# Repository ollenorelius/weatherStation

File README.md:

# weatherStation
A simple weather monitor based on an nRF52832 microcontroller

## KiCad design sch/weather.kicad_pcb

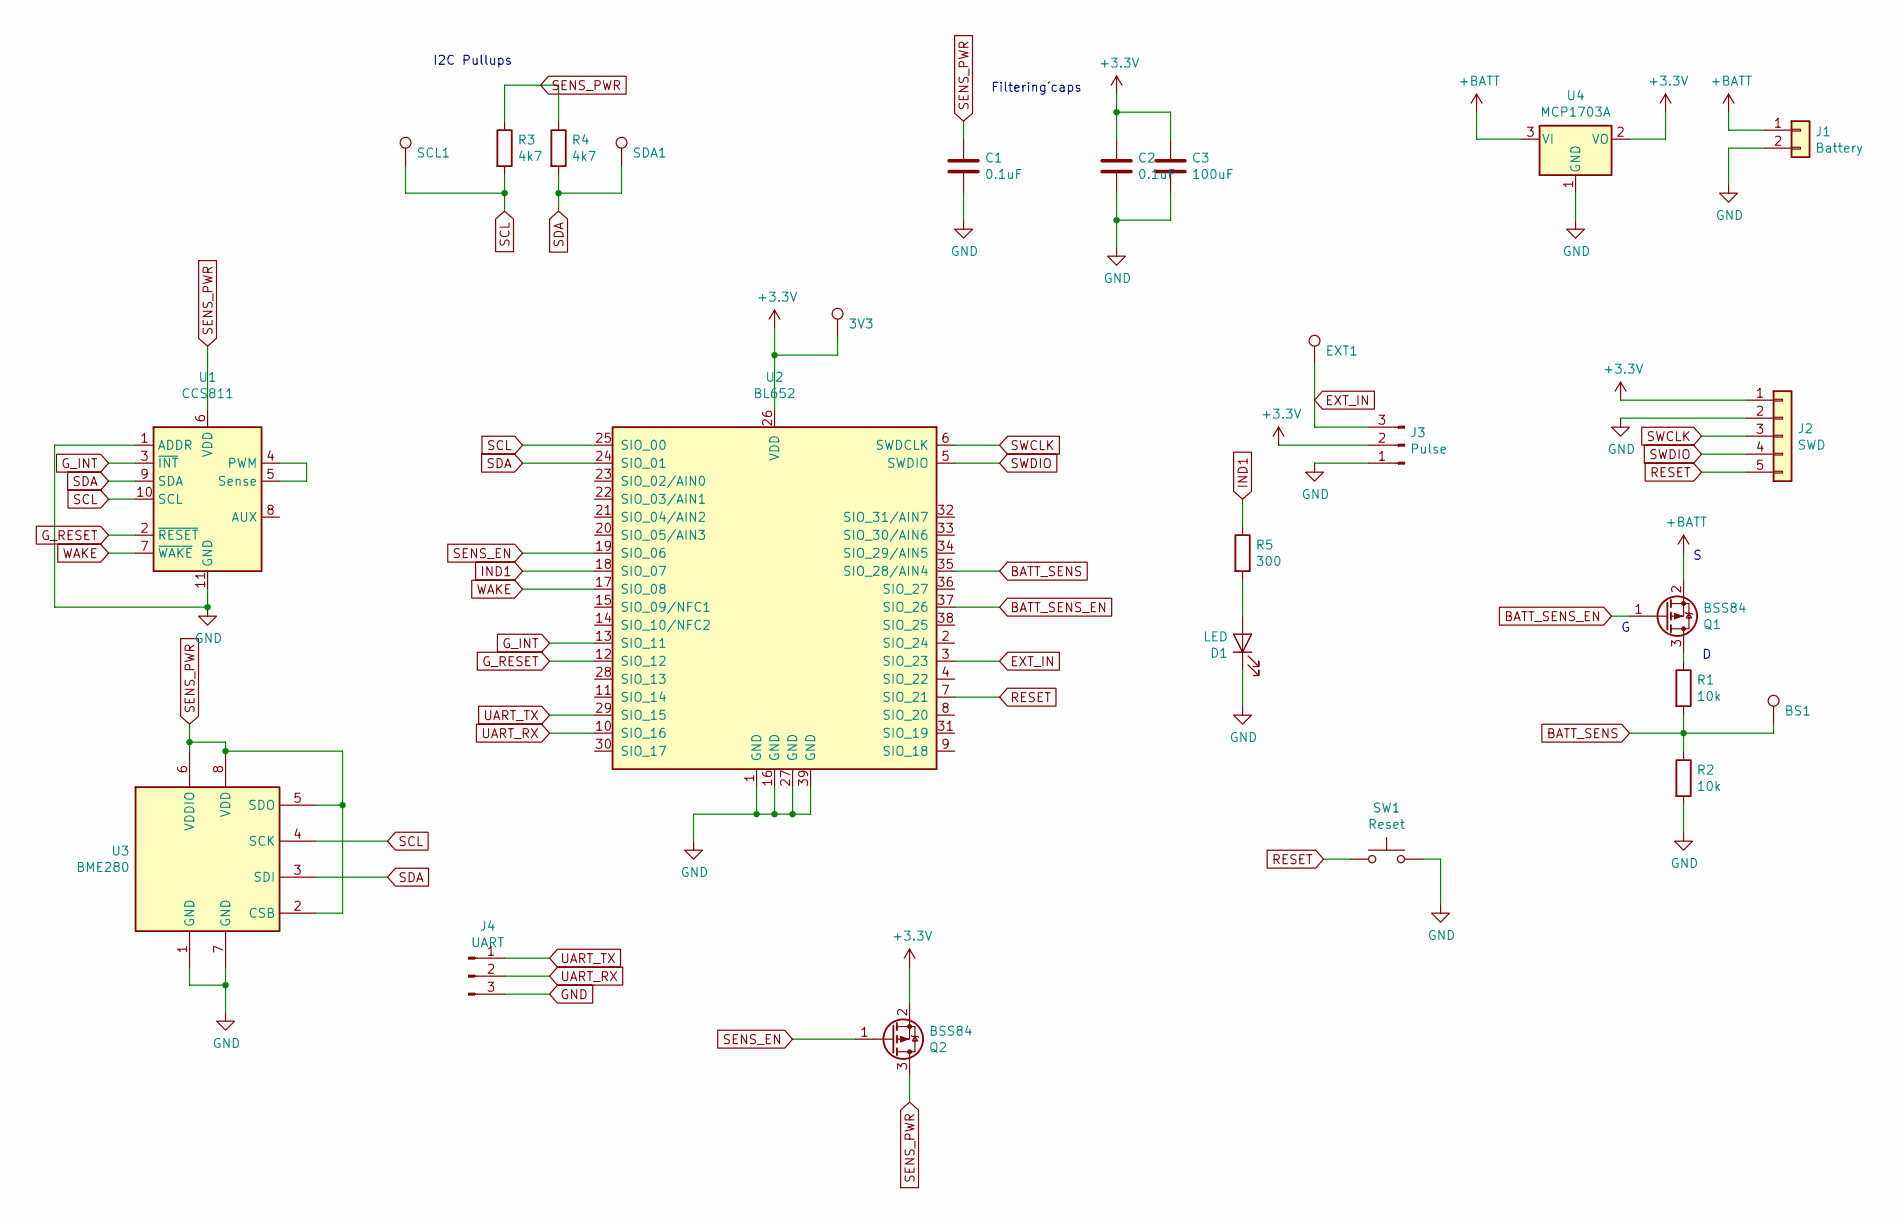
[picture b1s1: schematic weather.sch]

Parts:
3V3: TestPoint; TestPoint_Pad_D2.0mm
BS1: TestPoint; TestPoint_Pad_D2.0mm
C1, C2: 0.1uF; C_0805_2012Metric
C3: 100uF; C_1206_3216Metric
D1: LED; LED_0805_2012Metric
EXT1: TestPoint; TestPoint_Pad_D2.0mm
J1: Battery; JST_PH_S2B-PH-K_1x02_P2.00mm_Horizontal
J2: SWD; PinHeader_1x05_P2.54mm_Vertical
J3: Pulse; PinHeader_1x03_P2.54mm_Vertical
J4: UART; PinSocket_1x03_P2.54mm_Vertical
Q1, Q2: BSS84; SOT-23
R1, R2: 10k; R_0603_1608Metric
R3, R4: 4k7; R_0603_1608Metric
R5: 300; R_0603_1608Metric
SCL1: TestPoint; TestPoint_Pad_D2.0mm
SDA1: TestPoint; TestPoint_Pad_D2.0mm
SW1: Reset; SW_PUSH_6mm
U1: CCS811; AMS_LGA-10-1EP_2.7x4mm_P0.6mm
U2: BL652; Laird_BL652
U3: BME280; Bosch_LGA-8_2.5x2.5mm_P0.65mm_ClockwisePinNumbering
U4: MCP1703A; SOT-23

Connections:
+3V3: 3V3.1, C2.1, C3.1, J2.1, J3.2, Q2.2 (S), U2.26 (VDD), U4.2 (VO)
+BATT: J1.1, Q1.2 (S), U4.3 (VI)
BATT_SENS: BS1.1, R1.2, R2.1, U2.35 (SIO_28/AIN4)
BATT_SENS_EN: Q1.1 (G), U2.37 (SIO_26)
EXT_IN: EXT1.1, J3.3, U2.3 (SIO_23)
GND: C1.2, C2.2, C3.2, D1.1 (K), J1.2, J2.2, J3.1, J4.3, R2.2, SW1.2, U1.1 (ADDR), U1.11 (GND), U2.1 (GND), U2.16 (GND), U2.27 (GND), U2.39 (GND), U3.1 (GND), U3.7 (GND), U4.1 (GND)
G_INT: U1.3 (~INT), U2.13 (SIO_11)
G_RESET: U1.2 (~RESET), U2.12 (SIO_12)
IND1: R5.1, U2.18 (SIO_07)
unnamed: D1.2 (A), R5.2
unnamed: Q1.3 (D), R1.1
unnamed: U1.4 (PWM), U1.5 (Sense)
RESET: J2.5, SW1.1, U2.7 (SIO_21)
SCL: R3.2, SCL1.1, U1.10 (SCL), U2.25 (SIO_00), U3.4 (SCK); also elsewhere on the board
SDA: R4.2, SDA1.1, U1.9 (SDA), U2.24 (SIO_01), U3.3 (SDI); also elsewhere on the board
SENS_EN: Q2.1 (G), U2.19 (SIO_06)
SENS_PWR: C1.1, Q2.3 (D), R3.1, R4.1, U1.6 (VDD), U3.2 (CSB), U3.5 (SDO), U3.6 (VDDIO), U3.8 (VDD)
SWCLK: J2.3, U2.6 (SWDCLK)
SWDIO: J2.4, U2.5 (SWDIO)
UART_RX: J4.2, U2.10 (SIO_16)
UART_TX: J4.1, U2.29 (SIO_15)
WAKE: U1.7 (~WAKE), U2.17 (SIO_08)

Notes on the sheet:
I2C Pullups
Filtering´caps

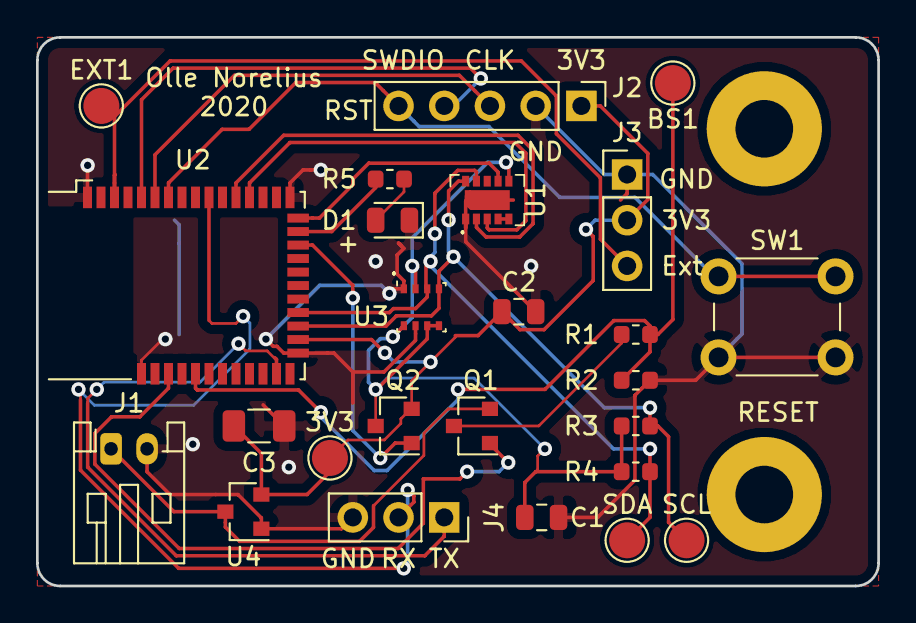
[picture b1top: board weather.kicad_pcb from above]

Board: 2 copper layers, 46.7 x 30.5 mm, 25 parts (0 on the bottom side), 22 nets.

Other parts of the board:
SCL: TestPoint; TestPoint_Pad_D2.0mm
SDA: TestPoint; TestPoint_Pad_D2.0mm

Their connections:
SCL: SCL.1; also elsewhere on the board
SDA: SDA.1; also elsewhere on the board

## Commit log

2020-09-24 Added schematics
